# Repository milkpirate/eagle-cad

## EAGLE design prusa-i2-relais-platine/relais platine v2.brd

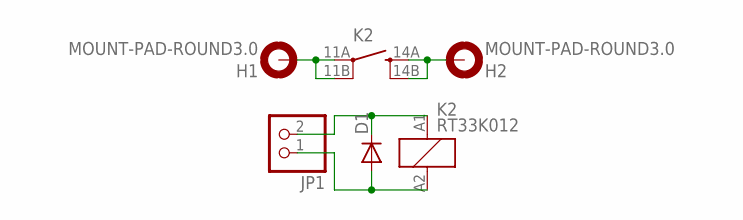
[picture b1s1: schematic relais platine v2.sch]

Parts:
D1: DIODE-D-5; D-5
H1, H2: MOUNT-PAD-ROUND3.0; 3,0-PAD
JP1: PINHD-1X2; 1X02
K2: RT33K012; RT-N/O16A5

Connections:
IN: H1.B3,0, K2.11A (PA), K2.11B (PB)
unnamed: D1.C, JP1.2, K2.A1 (1)
unnamed: D1.A, JP1.1, K2.A2 (2)
OUT: H2.B3,0, K2.14A (SA), K2.14B (SB)

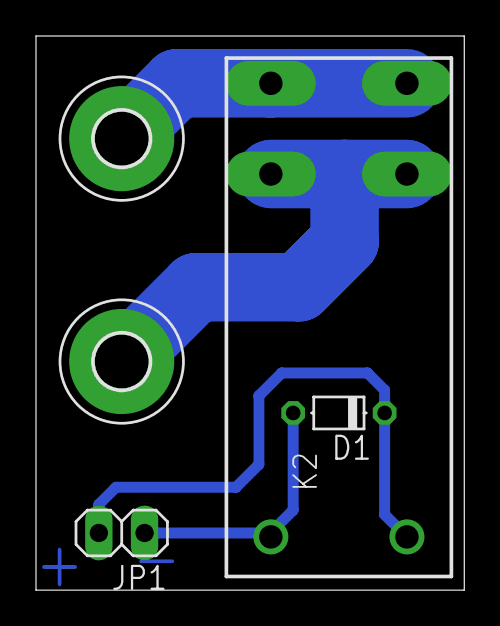
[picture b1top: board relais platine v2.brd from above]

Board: 2 copper layers, 23.8 x 30.8 mm, 5 parts (0 on the bottom side), 4 nets.

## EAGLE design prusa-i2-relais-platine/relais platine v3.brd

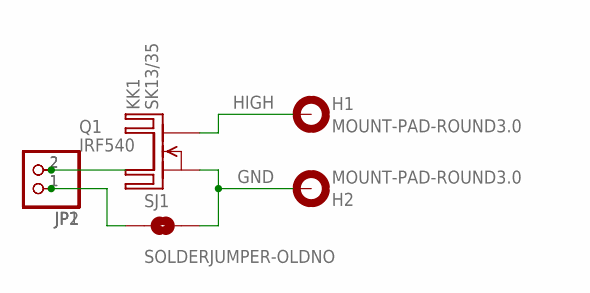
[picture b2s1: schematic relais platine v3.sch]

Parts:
H1, H2: MOUNT-PAD-ROUND3.0; 3,0-PAD
JP1: PINHD-1X2; 1X02
JP2: PINHD-1X2/90; 1X02/90
KK1: SK13/35
Q1: IRF540; TO220
SJ1: SOLDERJUMPER-OLDNO; SJ_2S-NO

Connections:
GND: H2.B3,0, Q1.3 (S), SJ1.2
HIGH: H1.B3,0, Q1.2 (D)
unnamed: JP1.1, JP2.1, SJ1.1
unnamed: JP1.2, JP2.2, Q1.1 (G)

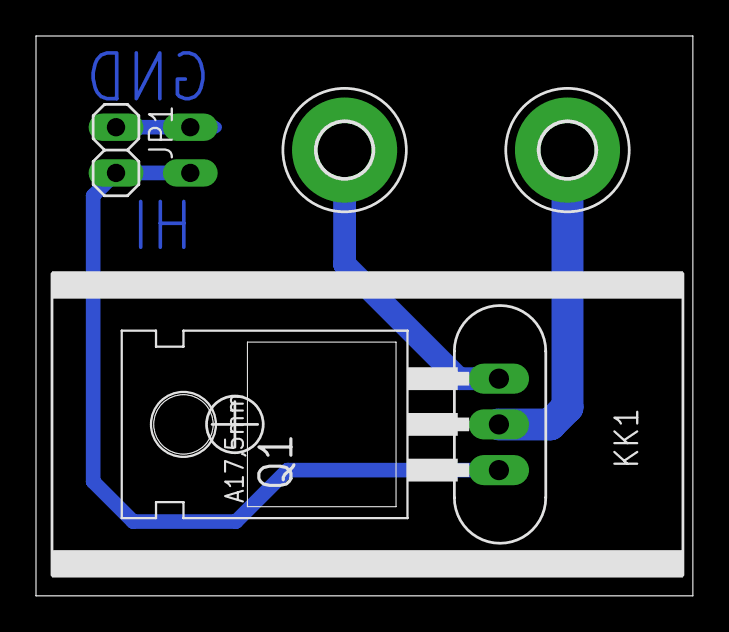
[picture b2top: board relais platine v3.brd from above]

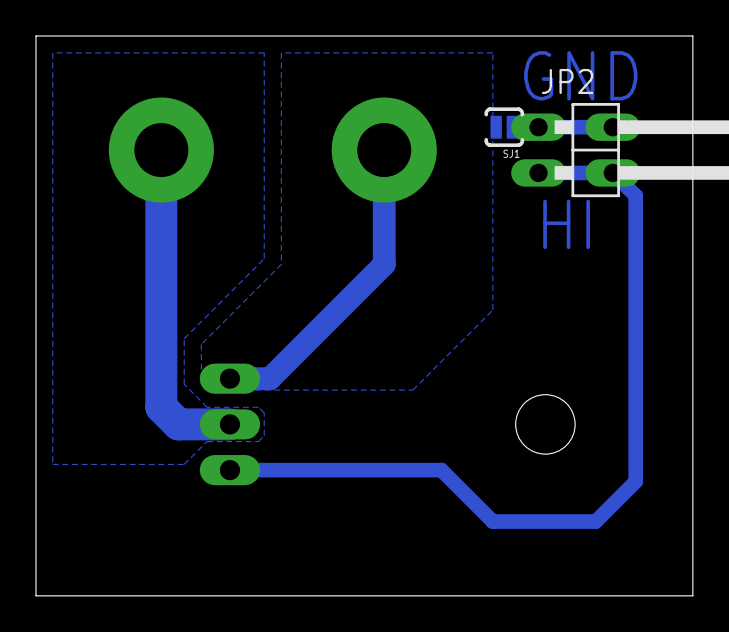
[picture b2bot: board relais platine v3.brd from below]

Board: 2 copper layers, 36.5 x 31.1 mm, 7 parts (2 on the bottom side), 4 nets.

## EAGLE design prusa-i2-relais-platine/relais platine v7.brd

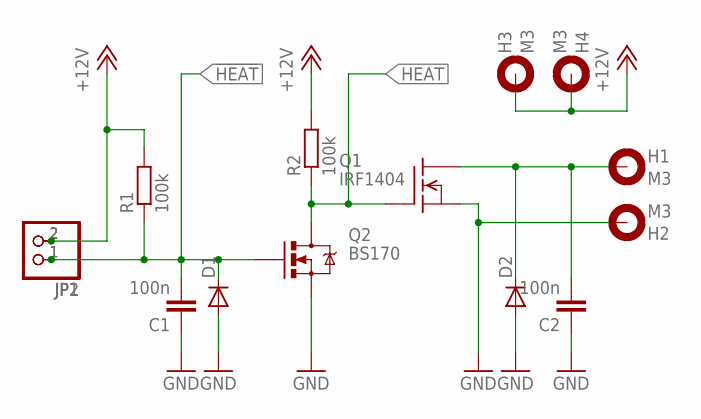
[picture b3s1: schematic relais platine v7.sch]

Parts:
C1, C2: 100n; C0805K
D1, D2: DIODE-MINIMELF; MINIMELF
H1, H2, H3, H4: M3; 3,0-PAD
JP1: PINHD-1X2; 1X02
JP2: PINHD-1X2/90; 1X02/90
Q1: IRF1404; TO220
Q2: BS170; SOT23-3
R1, R2: 100k; M0805

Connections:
!HEAT: C1.2, D1.C, JP1.1, JP2.1, Q2.1 (G), R1.1
+12V: H3.B3,0, H4.B3,0, JP1.2, JP2.2, R1.2, R2.2
GND: C1.1, C2.1, D1.A, D2.A, H2.B3,0, Q1.3 (S), Q2.2 (S)
HEAT: Q1.1 (G), Q2.3 (D), R2.1
HIGH: C2.2, D2.C, H1.B3,0, Q1.2 (D)

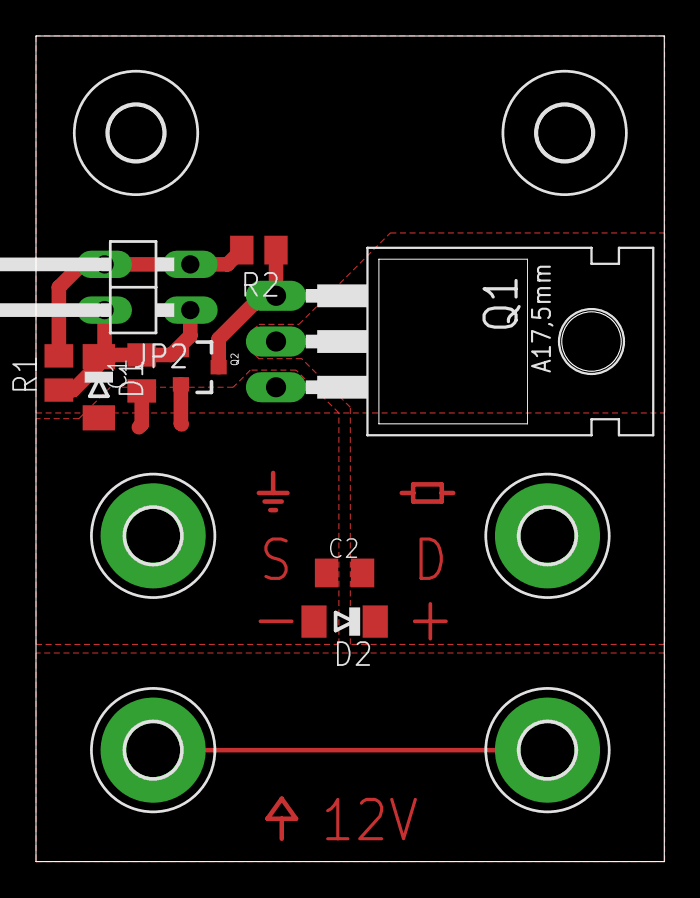
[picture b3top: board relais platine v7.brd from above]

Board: 2 copper layers, 34.9 x 45.9 mm, 16 parts (1 on the bottom side), 5 nets.

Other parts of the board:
U$1, U$2: 3,0

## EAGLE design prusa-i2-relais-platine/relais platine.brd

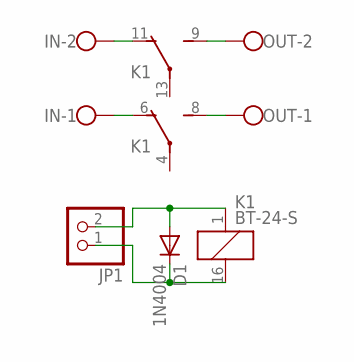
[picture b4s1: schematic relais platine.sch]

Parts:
D1: 1N4004; DO41-10
IN: W237-102
JP1: PINHD-1X2/90; 1X02/90
K1: BT-24-S; BT-XX-S
OUT: W237-102

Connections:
unnamed: K1.8 (S), OUT.1
unnamed: IN.2, K1.11 (O)
unnamed: K1.9 (S), OUT.2
unnamed: IN.1, K1.6 (O)
unnamed: D1.A, JP1.2, K1.1
unnamed: D1.C, JP1.1, K1.16 (2)

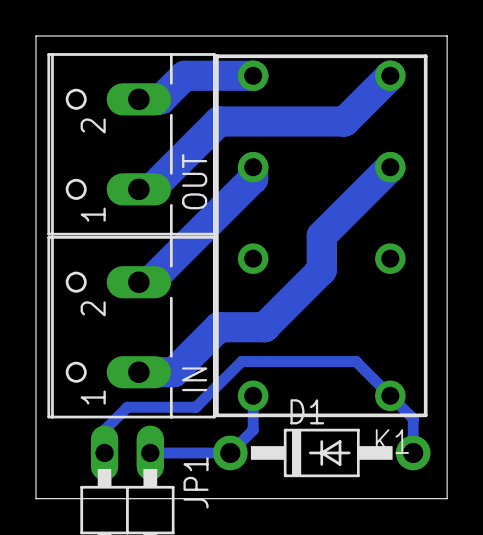
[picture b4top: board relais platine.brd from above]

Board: 2 copper layers, 22.8 x 25.7 mm, 5 parts (0 on the bottom side), 6 nets.

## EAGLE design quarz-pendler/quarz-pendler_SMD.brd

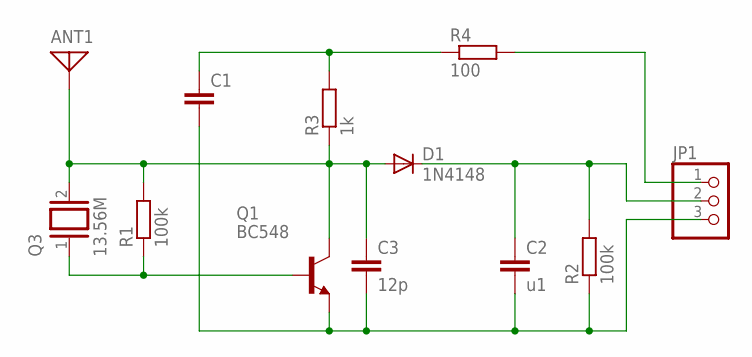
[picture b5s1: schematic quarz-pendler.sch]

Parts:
ANT1: ANTENNA; PAD-01
C1: C-EU025-025X050; C025-025X050
C2: u1; C025-025X050
C3: 12p; C025-025X050
D1: 1N4148; D-2.5
JP1: PINHD-1X3; 1X03
Q1: BC548; TO92-EBC
Q3: 13.56M; Q
R1, R2: 100k; 0207/2V
R3: 1k; 0207/2V
R4: 100; 0207/2V

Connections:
+5: JP1.1, R4.2
DAT: C2.1, D1.C, JP1.2, R2.2
GND: C1.2, C2.2, C3.2, JP1.3, Q1.E, R2.1
unnamed: ANT1.1, C3.1, D1.A, Q1.C, Q3.2, R1.2, R3.1
unnamed: Q1.B, Q3.1, R1.1
unnamed: C1.1, R3.2, R4.1

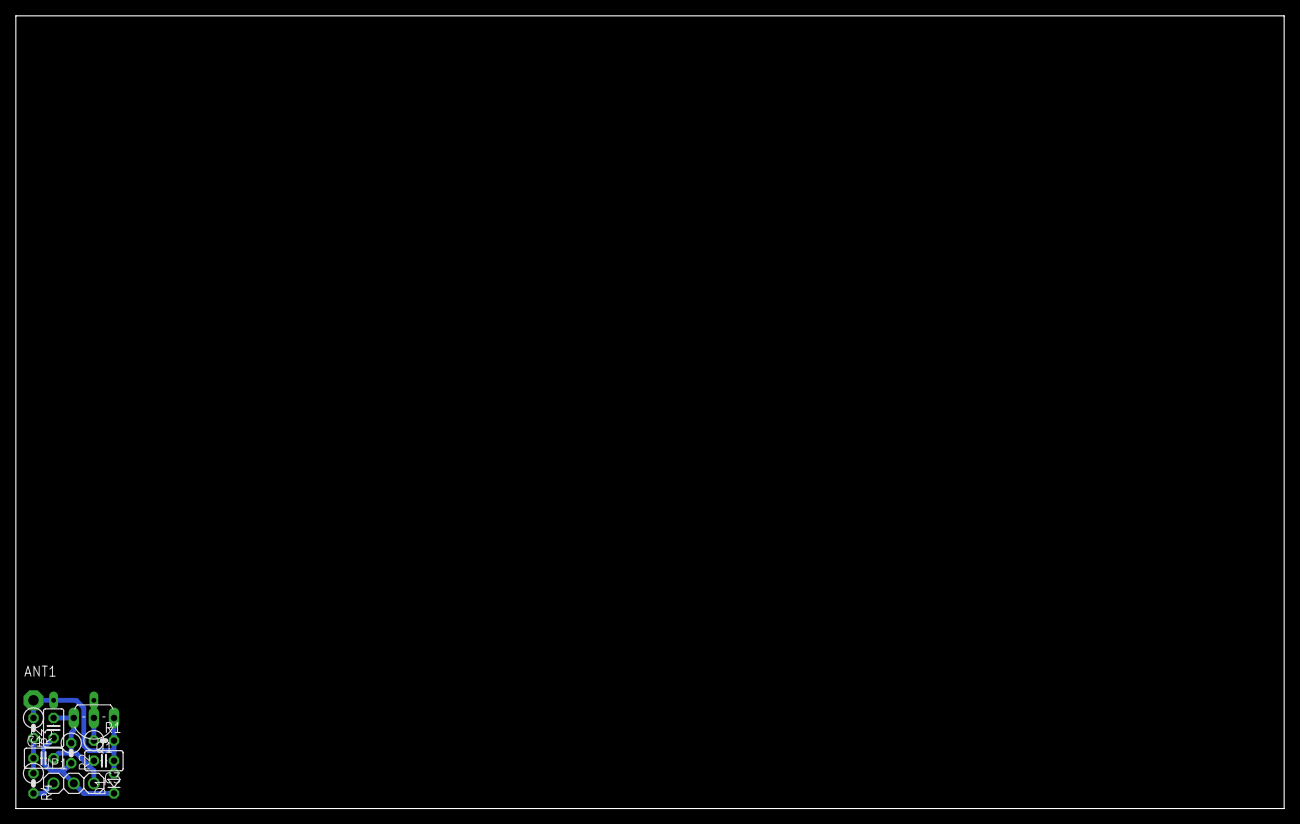
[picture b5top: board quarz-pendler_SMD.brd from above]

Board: 2 copper layers, 160.0 x 100.0 mm, 12 parts (1 on the bottom side), 6 nets.

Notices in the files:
parts and their libraries:
SparkFun-Retired: Licensing:Creative Commons ShareAlike 4.0 International - https://creativecommons.org/licenses/by-sa/4.0
